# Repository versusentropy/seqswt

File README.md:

# seqswt eurorack 4(3,2) to 1 sequential switch

## v0.9

Known bug: Label 2 and 3 at the switch are reversed.

  * 4hp
  * +/-12V 10mA/1mA
  * 1 PCB 2 layer
  * common jack is connected to one output at a time
    * DG412 Rail2Rail analog switch recommended
  * step input
    * move to next position
    * TN pin header on pcb
  * reset input
    * move to step 1
    * locked on step 1, while gate high.
<!---->

Schematic and layout with KiCad 5. Panel with Inkscape + shenzen2svg → Kicad

Ordered mine at JLCPCB. Added ICs by hand. Gerbers include marking for order number. BOM with part numbers for their assembly service.

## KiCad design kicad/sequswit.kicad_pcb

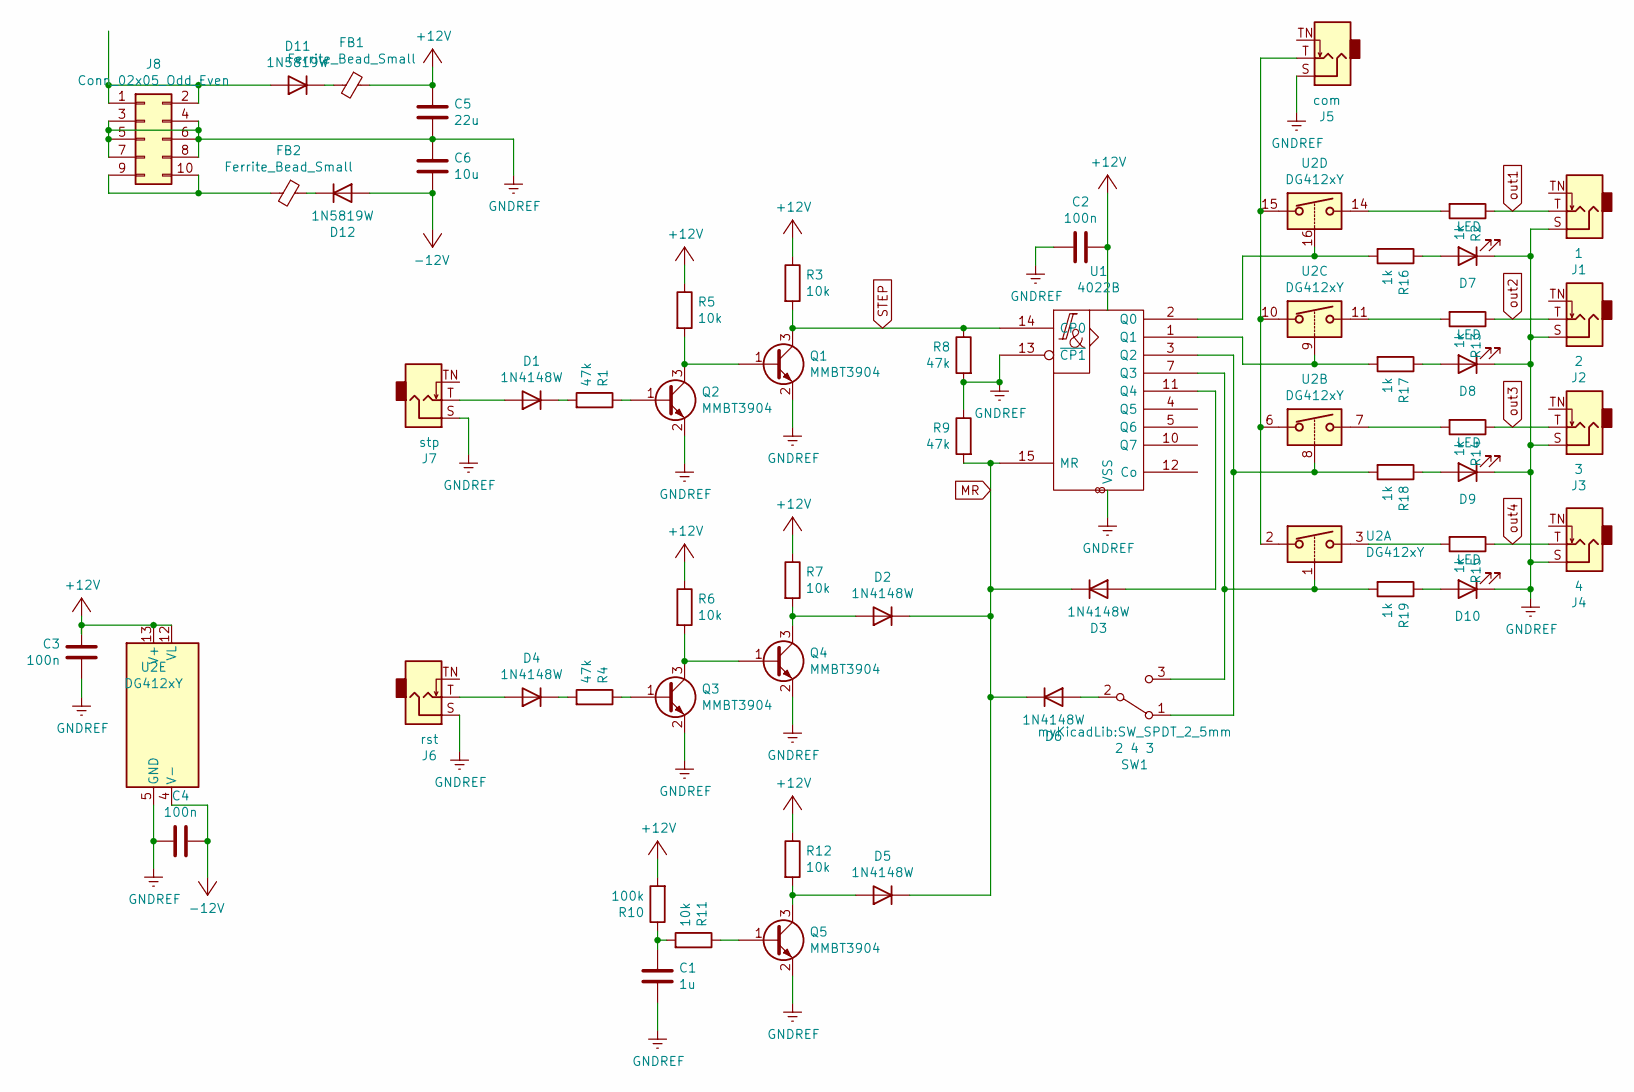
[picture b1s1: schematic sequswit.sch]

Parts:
C1: 1u; C_0402_1005Metric; LCSC C52923
C2, C3, C4: 100n; C_0402_1005Metric; LCSC C1525
C5: 22u; C_0805_2012Metric; LCSC C45783
C6: 10u; C_0805_2012Metric; LCSC C15850
D1, D2, D3, D4, D5, D6: 1N4148W; D_SOD-123; LCSC C81598
D7, D8, D9, D10: LED; LED_D3.0mm
D11, D12: 1N5819W; D_SOD-123; LCSC C402219
FB1, FB2: Ferrite_Bead_Small; L_0805_2012Metric; LCSC C1017
J1: 1; Jack_3.5mm_QingPu_WQP-PJ398SM_Vertical_CircularHolesSMALL
J2: 2; Jack_3.5mm_QingPu_WQP-PJ398SM_Vertical_CircularHolesSMALL
J3: 3; Jack_3.5mm_QingPu_WQP-PJ398SM_Vertical_CircularHolesSMALL
J4: 4; Jack_3.5mm_QingPu_WQP-PJ398SM_Vertical_CircularHolesSMALL
J5: com; Jack_3.5mm_QingPu_WQP-PJ398SM_Vertical_CircularHolesSMALL
J6: rst; Jack_3.5mm_QingPu_WQP-PJ398SM_Vertical_CircularHolesSMALL
J7: stp; Jack_3.5mm_QingPu_WQP-PJ398SM_Vertical_CircularHolesSMALL
J8: Conn_02x05_Odd_Even; PinHeader_2x05_P2.54mm_Vertical
Q1, Q2, Q3, Q4, Q5: MMBT3904; SOT-23; LCSC C20526
R1, R4, R8, R9: 47k; R_0402_1005Metric; LCSC C25792
R2, R13, R14, R15: 1k; R_1206_3216Metric; LCSC C4410
R3, R5, R6, R7, R11, R12: 10k; R_0402_1005Metric; LCSC C25744
R10: 100k; R_0402_1005Metric; LCSC C25741
R16, R17, R18, R19: 1k; R_0603_1608Metric; LCSC C21190
SW1: 2 4 3; SW_SPDT_2_5mm
U1: 4022B; TSSOP-16_4.4x5mm_P0.65mm; Mouser 595-CD4022BPWR
U2: DG412xY; SOIC-16_3.9x9.9mm_P1.27mm; Mouser 700-DG412DYT

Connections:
+12V: C2.2, C3.2, C5.1, FB1.1, R3.1, R5.1, R6.1, R7.1, R10.2, R12.1, U1.16 (VDD), U2.12 (VL), U2.13 (V+)
-12V: C4.1, C6.2, D12.2 (A), U2.4 (V-)
GNDREF: C1.1, C2.1, C3.1, C4.2, C5.2, C6.1, D7.1 (K), D8.1 (K), D9.1 (K), D10.1 (K), J1.S, J2.S, J3.S, J4.S, J5.S, J6.S, J7.S, J8.3, J8.4, J8.5, J8.6, J8.7, J8.8, Q1.2 (E), Q2.2 (E), Q3.2 (E), Q4.2 (E), Q5.2 (E), R8.2, R9.1, U1.8 (VSS), U1.13 (~CP1), U2.5 (GND)
MR: D2.1 (K), D3.1 (K), D5.1 (K), D6.1 (K), R9.2, U1.15 (MR)
unnamed: C1.2, R10.1, R11.2
unnamed: D1.1 (K), R1.2
unnamed: D1.2 (A), J7.T
unnamed: D2.2 (A), Q4.3 (C), R7.2
unnamed: D3.2 (A), U1.11 (Q4)
unnamed: D4.1 (K), R4.2
unnamed: D4.2 (A), J6.T
unnamed: D5.2 (A), Q5.3 (C), R12.2
unnamed: D6.2 (A), SW1.2 (B)
unnamed: D7.2 (A), R16.1
unnamed: D8.2 (A), R17.1
unnamed: D9.2 (A), R18.1
unnamed: D10.2 (A), R19.1
unnamed: D11.1 (K), FB1.2
unnamed: D11.2 (A), J8.1, J8.2
unnamed: D12.1 (K), FB2.1
unnamed: FB2.2, J8.9, J8.10
unnamed: J5.T, U2.2, U2.6, U2.10, U2.15
unnamed: Q1.1 (B), Q2.3 (C), R5.2
unnamed: Q2.1 (B), R1.1
unnamed: Q3.1 (B), R4.1
unnamed: Q3.3 (C), Q4.1 (B), R6.2
unnamed: Q5.1 (B), R11.1
unnamed: R2.2, U2.14
unnamed: R13.2, U2.11
unnamed: R14.2, U2.7
unnamed: R15.2, U2.3
unnamed: R16.2, U1.2 (Q0), U2.16
unnamed: R17.2, U1.1 (Q1), U2.9
unnamed: R18.2, SW1.1 (A), U1.3 (Q2), U2.8
unnamed: R19.2, SW1.3 (C), U1.7 (Q3), U2.1
STEP: Q1.3 (C), R3.2, R8.1, U1.14 (CP0)
out1: J1.T, R2.1
out2: J2.T, R13.1
out3: J3.T, R14.1
out4: J4.T, R15.1

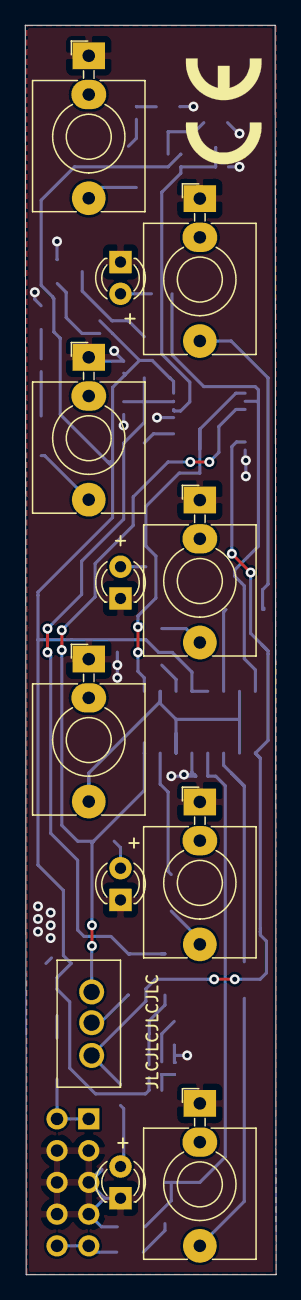
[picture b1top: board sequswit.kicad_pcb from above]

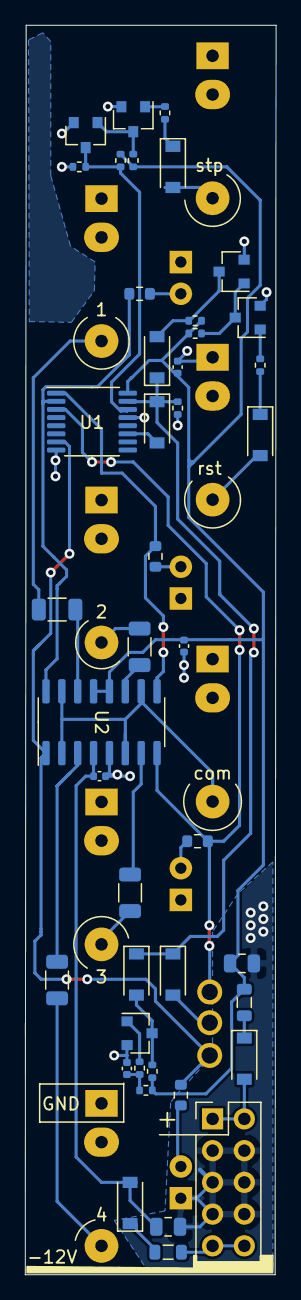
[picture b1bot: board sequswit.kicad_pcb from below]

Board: 2 copper layers, 20.1 x 100.0 mm, 55 parts (43 on the bottom side), 40 nets.

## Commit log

2021-11-26 start
2021-11-26 remove missing image

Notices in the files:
kicad/sequswit.kicad_pcb:
CC BY-NC-SA
